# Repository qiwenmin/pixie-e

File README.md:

# Pixie-E

Version 02 / BG1REN / 2019-12-06

## 简介

Pixie-E在经典的Pixie QRPP CW电台的基础上，做了些改进：

* 由单片机生成侧音，并增加了静音电路，提升发射时的体验；
* 增加了自动键功能，同时也支持手键；
* 改进了低通滤波器，杂散发射指标优于-40dB。

Pixie-E的电路板大小为5cm x 5.5cm，四个角为圆角，可以和一块9V电池一起安装在润喉糖盒子中。

<div class="display:flex">

</div>

## 关于元件

### 独石电容的容量

独石电容大多以三位数字表示容量。如果电容上标识的数字是nnm，其容量为：

$$
C = nn \times 10^{m} pF
$$

例如：

* 103： $10 \times 10^3 pF = 10 nF$
* 471： $47 \times 10^1 pF = 470 pF$

容量不到100pF的独石电容，有的以类似100（10p）、220（22p）这样的方式标识，也有的只用两位数字加字母p标识，例如22p、56p等。需要准确辨认。

### DIP-8封装的集成电路的方向

DIP-8封装的集成电路，在管脚1、8的一侧，有一个缺口。这个缺口方向要和电路板上丝印的缺口方向一致。使用集成电路插座时，插座的缺口方向也需要保持一致。

### 二极管的极性

<div class="display:flex">

</div>

如图所示，1N4148有环形标识的一侧为负极，另一侧为正极。发光二极管LED的长脚为正极，短脚为负极。

在电路板上，二极管的两个焊盘：圆形的为正极、方形的为负极。

### 电解电容

<div class="display:flex">
    
</div>

电解电容也是有极性的，不能装反。长脚为正极、短脚为负极。在电解电容上，负极也有专门的标识。

在电路板上，有白色填充的一侧为负极（圆形焊盘），另一侧为正极（方形焊盘，旁边有``+``标识）。

### 电源

电源一定不能接反！电路板上标识``VCC``的一侧是电源正极、标识``GND``的一侧是电源负极。

## 焊接与装配

<div class="display:flex">

</div>

由于Pixie-E的电路简单、元件比较少，既可以分模块装配，也可以按照元件从矮到高的顺序装配。下面以40米波段为例，介绍装配顺序。20米波段见后文的说明。

以从矮到高的顺序装配：

* 两个IC插座
* 音频插座和电键插座
* 独石电容、可变电容
* 晶振（如果用49S矮晶振）
* 微动按钮、开关、电源插座
* 三极管（BJT）、场效应管（FET）、78L05稳压器
* 电阻
* 二极管（有环形标识的一侧为负极）、发光二极管（长脚为正极）
* 电解电容
* 天线插座
* 晶振（如果用49U高晶振）

分模块装配：

* 装配电源模块：
  * [ ] 电源插座（J1）：一定要注意极性，不能装反！！！
  * [ ] 开关（SW1）
  * [ ] R12：4.7K
  * [ ] D3：黄色LED（长脚为正极）
  * 完成后，插入电源，打开开关，应该能点亮黄色LED
* 装配振荡器：
  * [ ] Q1：2N2222
  * [ ] 晶振Y1：7.023MHz
  * [ ] 可调电容C1、C2：60p
  * [ ] D1：1N4148（有环形标识的一侧为负极）
  * [ ] R1：47K
  * [ ] R2：470
  * [ ] C3：100p
  * [ ] C4：100p
  * [ ] C5：10n
  * 完成后，接入电源，打开开关，振荡器应该工作，在C5处能检测到本振信号。如果没有示波器，可以用一个电台在附近收听（接收频率调整到晶振的频率附近），应该能收到本振电路辐射出来的信号。
* 装配放大/混频级：
  * [ ] Q2：2N2222
  * [ ] R3：47K
  * [ ] R4：10K
  * [ ] C6：47n
  * [ ] C7：10n
  * [ ] C8：100n
  * [ ] L1：100u
  * [ ] L2：22u
  * 完成后，通电，应能从C7处检测到本振信号。
* 装配低通滤波器和天线插座：
  * [ ] L3：1u
  * [ ] L4：1u
  * [ ] C13：470p
  * [ ] C15：470p
  * [ ] C14：1n
  * [ ] C16：100p
  * [ ] 天线插座J2
  * 完成后，通电，应能在天线插座检测到本振信号。
* 装配单片机及外围元件：
  * [ ] 单片机U2：STC15W104
  * [ ] 稳压器U3：78L05
  * [ ] Q3：2N2222
  * [ ] R7：2K
  * [ ] R9：2K
  * [ ] R8：1K
  * [ ] D2：红色LED（长脚为正极）
  * [ ] Q4：2N3906
  * [ ] R10：4.7K
  * [ ] R11：4.7K
  * [ ] Q5：2N7000
  * [ ] R13：4.7K
  * [ ] C17：100n
  * [ ] R14：10K
  * [ ] R15：100
  * [ ] 音频插座J3
  * [ ] 电键插座J4
  * [ ] 微动开关SW2
  * 完成后，接假负载、接耳机（或有源音箱）、接电键（手键或自动键均可）。接通电源，应能听到自动键电路发出的提示声；按动电键，应能听到发报侧音，并能看到红色LED闪烁；按动微动开关，应开始自动发报；检测假负载，应能检测到发报的信号（用示波器或用另外一个电台在附近接收）。
* 装配音频放大电路：
  * [ ] U1：LM386
  * [ ] R5：1K
  * [ ] R6：10
  * [ ] 电解电容C9：10u
  * [ ] 电解电容C10：100u
  * [ ] C11：10n
  * [ ] 电解电容C12：10u
  * 完成后，通电，应能从耳机或有源音箱中听到背景噪声。用金属镊子碰触天线或LM386的第三脚，应能听到明显的噪声。

全部装配完成后，即可进行调试。

## 上电调试

接好假负载、耳机或有源音箱、手键，接通电源。这时应能从耳机或有源音箱中听到背景噪声。用金属镊子碰触天线或LM386的第三脚，应能听到明显的噪声。如果不正常，请仔细看电路图检查有无焊错、虚焊、短路等情况。

按下电键，应能听到发报侧音，并能看到红色LED闪烁；按动微动开关，应开始自动发报；检测假负载，应能检测到发报的信号（用示波器或用另外一个电台在附近接收）。

### 校准接收和发射频率

示波器或频率计接假负载。如果没有示波器或频率计，可以用另一个电台来帮助校准。

校准接收频率：调整C1，让振荡器的频率在7.0236MHz左右即可。如果没有示波器或频率计，可在旁边用一个电台于7.023Mhz频率发射，调整C1，让Pixie-E收到的声音听起来舒服即可。

校准发射频率：按下手键进行发射，调整C2，让振荡器的频率在7.023MHz左右即可。如果没有示波器或频率计，可在旁边用一个电台于7.023MHz频率接收，调整C2，让电台收到的信号听起来舒服即可。

### 设置自动键

请参照自动键手册完成自动键的设置。

### 输出功率

依据供电电压的不同，以及R2不同取值（见下文），发射功率约在200mW到600mW之间。

如果输出功率太低，首先检查有无虚焊、短路等焊接问题，其次检查Q1的放大倍数。Q1的放大倍数大于200比较好。

前面的调试都完成后，即可接入天线，进行通联。

## 20米波段

20米波段和40米波段有如下不同：

| 元件     | 40米波段 | 20米波段  |
| -------- | -------- | --------- |
| 晶振Y1   | 7.023MHz | 14.023MHz |
| L3、L4   | 1u       | 470n      |
| C13、C15 | 470p     | 220p      |
| C14      | 1n       | 470p      |
| C16      | 100p     | 68p       |

## 一些微调

### R2

R2可以选用220、470或1K。阻值越小，发射功率越大。在用9V电池供电的情况下，可以使用220。如果使用11V或更高的供电电压，则建议使用470或1K。

在使用小阻值、高电压的时候，需要注意Q2的发热情况。如果出现发射时Q2烫手的情况，则应该降低供电电压，或使用470/1K的阻值。

### R5

由于Pixie-E的供电电压可能会高于LM386的工作电压，因此用R5来保护。但引入R5会增加LM386的非线性，加强了广播干扰。

如果Pixie-E的供电电压低于12V，则可以短路R5，可以在一定程度上减轻广播干扰。

### R13

调整R13可以改变侧音音量。R13可以从1K到10K，阻值越大，侧音音量越小。

### R15

如果只用耳机，可以不接R15。用有源音箱的情况下，某些有源音箱的输入阻抗比较高，会造成侧音音量明显强于接收音量的情况，接入R15能改善这种情况，降低在接入有源音箱的情况下的侧音音量（但也会稍微降低接收音量）。

### C8

将C8改为22n或10n，可以降低收发切换时的开关声，改善体验。但同时也会降低接收音量。

### C16

不接C16，能提升大约10%左右的发射功率。但这会增加杂散发射，从优于-40dB变为-30dB，超过了相关标准。

## 元件清单

| 编号 | 值   | 说明 |
| ---- | ---- | ---- |
| C1 | 60p | 可调电容 |
| C2 | 60p | 可调电容 |
| C3 | 100p | 101 |
| C4 | 100p | 101 |
| C5 | 10n | 103 |
| C6 | 47n | 473 |
| C7 | 10n | 103 |
| C8 | 100n | 104 |
| C9 | 10u | 电解电容 |
| C10 | 100u | 电解电容 |
| C11 | 10n | 103 |
| C12 | 10u | 电解电容 |
| C13 | 470p | 471；20米波段为220p（221） |
| C14 | 1n | 102；20米波段为470p（471） |
| C15 | 470p | 471；20米波段为220p（221） |
| C16 | 100p | 101；20米波段为68p |
| C17 | 100n | 104 |
| D1 | 1N4148 | |
| D2 | LED | 红色发光二极管 |
| D3 | LED | 黄色发光二极管 |
| J1 | PWR | 电源插座 |
| J2 | ANT | SMA天线插座 |
| J3 | SP | 音频插座 |
| J4 | KEY | 电键插座 |
| L1 | 100u | |
| L2 | 22u | |
| L3 | 1u | |
| L4 | 1u | |
| Q1 | 2N2222 | |
| Q2 | 2N2222 |  |
| Q3 | 2N2222 | |
| Q4 | 2N3906 | |
| Q5 | 2N7000 | |
| R1 | 47K | |
| R2 | 470 | 可选220、470或1K |
| R3 | 47K | |
| R4 | 10K | |
| R5 | 1K | |
| R6 | 10 | |
| R7 | 2K | |
| R8 | 1K | |
| R9 | 2K | |
| R10 | 4.7K | |
| R11 | 4.7K | |
| R12 | 4.7K | |
| R13 | 4.7K | 可选1K到10K |
| R14 | 10K | |
| R15 | 100 | |
| SW1 | PWR | 电源开关 |
| SW2 | SW | 微动按钮 |
| U1 | LM386 | |
| U2 | STC15W104 | |
| U3 | LM78L05 | |
| Y1 | 7.023MHz | 晶振；20米波段为14.023MHz |

## 相关文档

* 《Pixie-E电路图》
* 《StcKeyer自动键说明书》

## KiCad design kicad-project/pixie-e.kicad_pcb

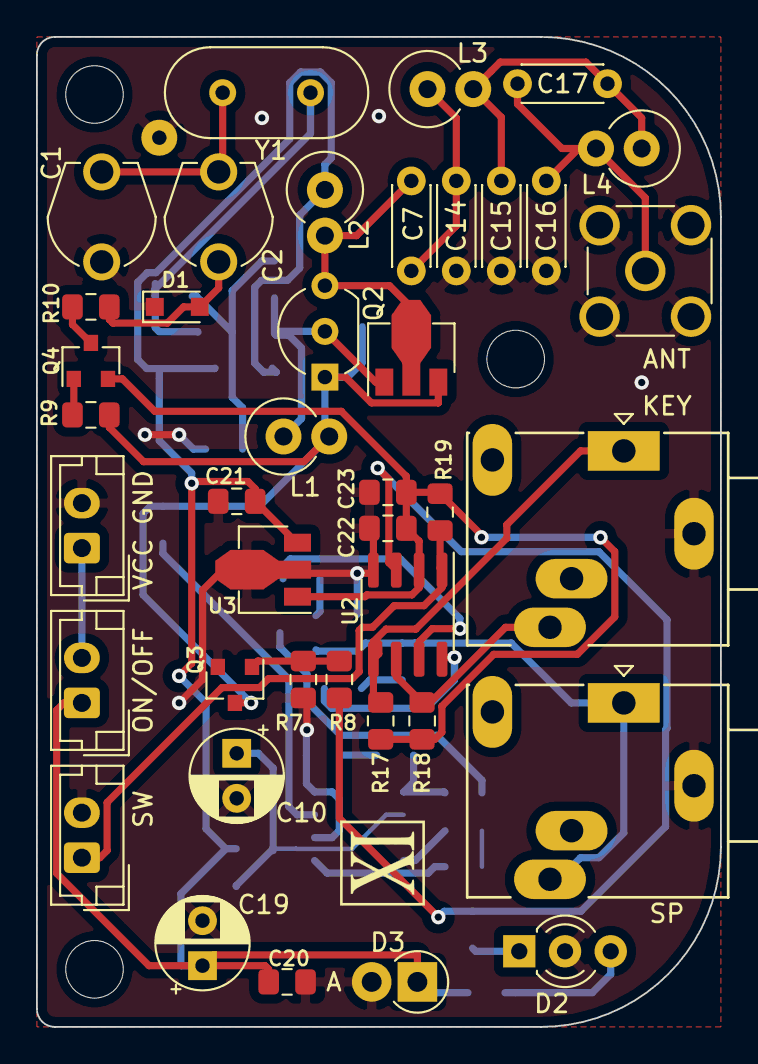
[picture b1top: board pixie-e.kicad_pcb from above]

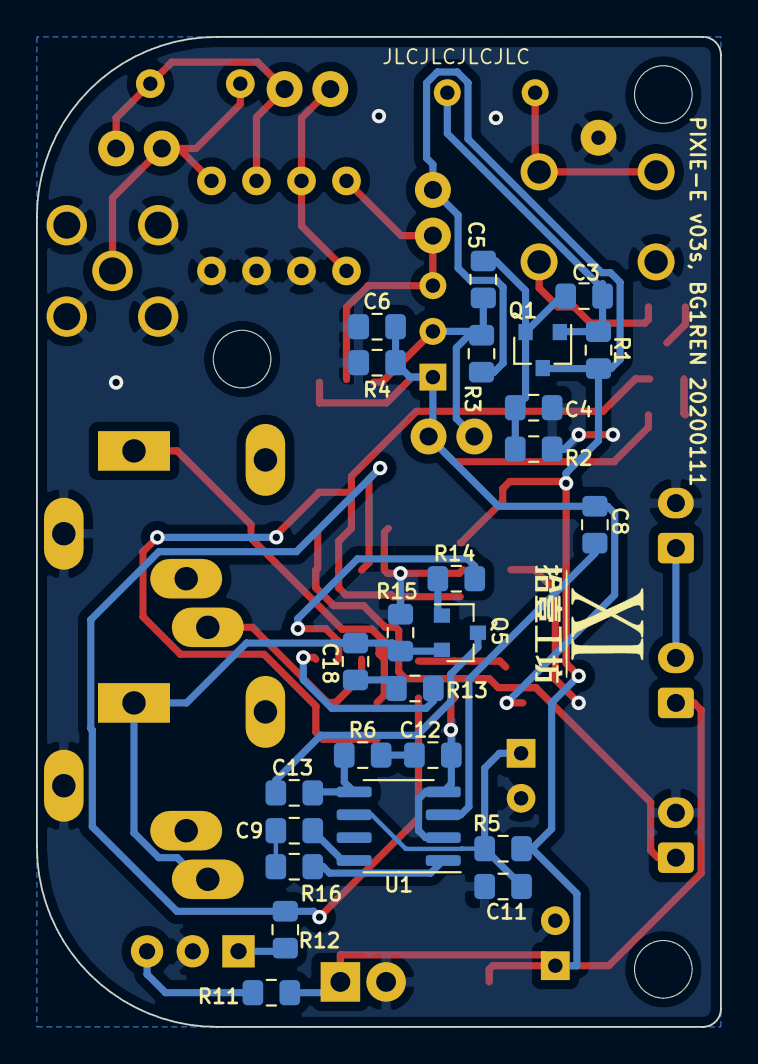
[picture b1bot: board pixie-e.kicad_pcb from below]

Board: 2 copper layers, 38.0 x 55.0 mm, 64 parts (25 on the bottom side), 36 nets.

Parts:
C1, C2: 60; TZ03-F
C3, C4: 100; C_0805_2012Metric_Pad1.15x1.40mm_HandSolder
C5, C12: 10n; C_0805_2012Metric_Pad1.15x1.40mm_HandSolder
C6: 47n; C_0805_2012Metric_Pad1.15x1.40mm_HandSolder
C7: 100n; C_Disc_D4.3mm_W1.9mm_P5.00mm
C8, C11, C18, C20, C22: 100n; C_0805_2012Metric_Pad1.15x1.40mm_HandSolder
C9, C13, C23: 10u; C_0805_2012Metric_Pad1.15x1.40mm_HandSolder
C10, C19: 100u; CP_Radial_D5.0mm_P2.50mm
C14, C16: 470; C_Disc_D4.3mm_W1.9mm_P5.00mm
C15: 1n; C_Disc_D4.3mm_W1.9mm_P5.00mm
C17: 100; C_Disc_D4.3mm_W1.9mm_P5.00mm
C21: 330n; C_0805_2012Metric_Pad1.15x1.40mm_HandSolder
D1: 1N4148; D_SOD-323_HandSoldering
D2: LED_Dual_ACA; LED_D3.0mm-3
D3: 1N4001; D_DO-41_SOD81_P2.54mm_Vertical_AnodeUp
J1: PWR; JST_EH_B2B-EH-A_1x02_P2.50mm_Vertical
J2: ANT; SMA_Molex_73251-2200_Horizontal
J3: SP; Jack_3.5mm_Ledino_KB3SPRS_Horizontal
J4: KEY; Jack_3.5mm_Ledino_KB3SPRS_Horizontal
L1: 100u; L_Axial_L9.5mm_D4.0mm_P2.54mm_Vertical_Fastron_SMCC
L2: 22u; L_Axial_L9.5mm_D4.0mm_P2.54mm_Vertical_Fastron_SMCC
L3, L4: 1u; L_Axial_L9.5mm_D4.0mm_P2.54mm_Vertical_Fastron_SMCC
Q1, Q3: 2N2222; SOT-23
Q2: 2N2222; TO-92_Inline_Wide
Q4: 2N3906; SOT-23
Q5: 2N7002; SOT-23
R1, R3: 47K; R_0805_2012Metric_Pad1.15x1.40mm_HandSolder
R2, R8, R10, R16: 1K; R_0805_2012Metric_Pad1.15x1.40mm_HandSolder
R4, R14, R17, R18, R19: 10K; R_0805_2012Metric_Pad1.15x1.40mm_HandSolder
R5, R6: 10; R_0805_2012Metric_Pad1.15x1.40mm_HandSolder
R7, R12: 2K; R_0805_2012Metric_Pad1.15x1.40mm_HandSolder
R9, R11, R13: 4.7K; R_0805_2012Metric_Pad1.15x1.40mm_HandSolder
R15: 100; R_0805_2012Metric_Pad1.15x1.40mm_HandSolder
SW1: ON/OFF; JST_EH_B2B-EH-A_1x02_P2.50mm_Vertical
SW2: SW; JST_EH_B2B-EH-A_1x02_P2.50mm_Vertical
U1: LM386; SOIC-8_3.9x4.9mm_P1.27mm
U2: STC15W104; SOIC-8_3.9x4.9mm_P1.27mm
U3: LM78L05_TO92; SOT-89-3
Y1: 7.023MHz; Crystal_HC49-U_Vertical

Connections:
5V: C22.2, C23.1, Q4.2, R17.2, R18.2, R19.2, U2.2, U3.1
/V+: C10.1, C11.2, R5.1, U1.6
AF: C13.2, Q5.3
ANT: C16.2, C17.1, J2.1, L4.2
DAH: J4.R, R18.1, U2.6
DIT: J4.T, R17.1, U2.5
GND: C1.2, C4.2, C6.2, C10.2, C11.1, C12.1, C14.1, C15.1, C16.1, C19.2, C20.1, C21.1, C22.1, C23.2, D1.1, D2.2, D3.2, J1.2, J2.2, J3.S, J4.S, Q3.2, R2.2, R4.2, R7.2, R15.2, SW2.2, U1.2, U1.4, U2.4, U3.2
KEY: C6.1, C8.1, L1.2, Q2.1, Q3.3, R4.1, R9.1
LPF: C7.1, C14.2, L3.1
MUTE: R14.1, U2.7
unnamed: C1.1, C2.1, Y1.2
unnamed: C3.1, Q1.1, R1.2, Y1.1
unnamed: C3.2, C4.1, C5.2, Q1.2, R2.1
unnamed: C5.1, L1.1, Q2.2, R3.2
unnamed: C7.2, L2.2, Q2.3
unnamed: C8.2, U1.3
unnamed: C9.1, R16.1
unnamed: C9.2, U1.8
unnamed: C12.2, R6.2
unnamed: C13.1, R6.1, U1.5
unnamed: C15.2, C17.2, L3.2, L4.1
unnamed: C18.2, R13.1
unnamed: D2.1, R12.2
unnamed: D2.3, R11.1
unnamed: J1.1, SW1.2
unnamed: Q3.1, R7.1, R8.1
unnamed: Q4.1, R9.2
unnamed: Q4.3, R10.2
unnamed: Q5.1, R14.2
unnamed: R16.2, U1.1
Phone: C18.1, J3.R, J3.T, Q5.2, R15.1
SHIFT: C2.2, D1.2, R10.1
SW: R19.1, SW2.1, U2.1
Sidetone: R13.2, U2.8
TX-LED: R8.2, R12.1, U2.3
VCC: C19.1, C20.2, C21.2, D3.1, L2.1, Q1.3, R1.1, R3.1, R5.2, R11.2, SW1.1, U3.3

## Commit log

2019-11-18 Change Q1 to 2N2222.
2019-11-18 Modify the firmware profile to pnm
2019-11-18 Update the TZ03 footprint
2019-11-18 Change the ee-libs url to https protocol.
2019-11-19 Update C2, 20m comment and page settings.
2019-11-19 Fix the typo of L3/L4.
2019-11-19 Add README.md - not finished.
2019-11-21 Remove a space.
2019-11-22 Change C16 to 68pF
2019-12-05 Fix: C14 1u -> 1n
2019-12-06 Fix typo
2019-12-20 Reduce the noise.
2019-12-24 Mod-20191224
2020-01-09 Upgrade ee-libs.
2020-01-13 Add .DS_Store to ignore list.
2020-01-13 Finish the 1st smt version.
